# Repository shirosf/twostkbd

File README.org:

* Two-stroke single hand keyboard
** Introduction
This is a following project to [[https://github.com/shirosf/binarykbd][Binary5 keyboard]]
The basic idea of this keyboard is as follows:
+ hit one of 6 keys twice: 36 codes
[[./photos/twostkbd_finger_maps1.png]]
+ 4 modifiers: 'shift','ctrl','alt', and one more 'ext'
[[./photos/twostkbd_finger_maps2.png]]
+ 3 function keys: 'SPACE','BACK SPACE','RETERN'
[[./photos/twostkbd_finger_maps3.png]]
All key maps can be changed by a configuration file

The total uses 13 keys.
26 of the 36 codes are used for alphabet character codes.
The other 10 are used for numerical character codes.
'ext' modifiers support symbol character codes.

** Hardware
KiCAD schematic and PCB data are in 'pcb' directory.
The HW consists of key switches, LEDs and Raspberry Pi Zero.
The circuits are mostly simple connections between GPIOs and switches.
#+ATTR_LATEX: :width 200px
#+ATTR_HTML: :width 200px
#+CAPTION: 14 keys and Raspberry Pi Zero
[[./photos/kbd_photo1.jpg]]

<2024-09-13 Fri>
Supported "Arduino Nano ESP32" to attach on PiZero connector.
#+ATTR_LATEX: :width 200px
#+ATTR_HTML: :width 200px
#+CAPTION: 13 keys and Arduin Nano ESP32
[[./photos/kbd_arduino1.jpg]]
It would be better to have both PiZero connector and Arduino Nano
connector on the PCB.
I would update the PCB design at the time of the next PCB order.
Arduino GBIO connections are defined in "key-gpio table" in "config.org"

** Arduino Software
Arduino project directory is "twskbino".
Go to the directory, then edit "Makefile" there to adjust to your hardware.
My Arduino board was an unofficial "esp32-s3" type board; to find out
"FBQN", I chose a looks-close one.
I believe that as long as it is "esp32-s3" type board "FBQN" should be okay.

To build and install from that Makefile, you need to install "arduino-cli"
and "esp32-s3" library.
Once they are ready, "make install" does all the jobs.

People who use IDE need a different way.

The way of configuration is the same as the PiZero Software.
Everything is defined in "config.org".

Arduino Nano has a RGB-LED on the board.
It starts with non-lighting status(R, G, B are all turned off).
'B' is ON when a key is pressed.
'G' is ON when any modifier key is pressed or locked.

** PiZero Software
*** Installation
Copy following 3 files into some directory of Pi Zero.
+ twostkbd.py, create_device.sh, config.org

Using included Makefile, "make sshcopy" copies the files by 'scp'.
It needs 'pizero' defined in ssh config.

*** Run
You go to the directory of the target Pi Zero where 3 files above are copied
by ssh or a local terminal.

At the first time after booting up, 'create_device.sh' needs to be run.
It creates a USB HID device: '/dev/hidg0'.

Once the USB HID device is created, 'twostkbd.py' can run, and it feeds
keyboard events into the device.

*** systemd service
To make the program start automatically at boot time, install "twostkbd.service"
and enable it as follows:
when you copy "twostkbd.py, create_device.sh, config.org" to the target Pi Zero,
you also copy "Makefile, twostkbd.service". Then go to the directory, and run the
following commands:
$ sudo make install
$ sudo make enable_service

When you changed the program or the config file in the working directory,
$ sudo make install
then restart the service again as next:
$ sudo systemctl restart twostkbd.service

*** Configuration
'twostkbd.py' reads 'config.org' file in the working directory.
'config.org' has the following 4 sections:
+ key-gpio table
  Each row defines,
  "schematic switch symbol","GPIO number","key name in this config file"
  Any key switch position can be changed in this table.
  E.G. swapping 'ctrl' and 'shift' in the table swaps the positions of 'ctrl' key
  and 'shift' key.

+ 6-key table
  Each row defines,
  assigned key: alphabet or number.
  '1st key' and '2nd key' combination by number, which is the number part of 'k*' name.
  modified key by the modifier key.
  The most of 'shift', 'alt', 'ctrl' modifier positions are empty.  In those cases the
  modifiers simply add the named modifier bits on the key events.

+ fkey table
  This table defines the function keys: f0 to f3.

+ multikeys table
  When more than 2 keys are pressed at the same time, it functions as "func" column
  defined function.

** License
Unless otherwise explicitly stated,
all files in this project are released under GNU General Public License Version 2.

** Development history
*** <2024-11-15 Fri>
With a half year practice, I come to around 25-WPM level.
And it seems to be saturated and the progress from this point will be very slow.
For some purposes, this keyboard could be useful.
But for my use, which is mostly writing program codes, it can't replace
regular 2-handed keyboards.

I stop this project at this point.

*** <2024-09-14 Sat>
+ Released the Arduino ESP32-S3 software.
PiZero runs a heavy Linux kernel and takes a long time to boot up.
There must be a room to improve by optimization, but I thought it
wouldn't come to my expected level.
With Arduino HW, connecting a USB cable, it becomes ready to use in a second.
Arduino supports a very convenient USBHIDKeyboard library; thanks to it
developing the software was easy.

+ Created a new board which uses "[[http://www.kailh.com/en/Products/Ks/CS/][Kailh Choc Switch]], Red".
[[./photos/choc_sw_pink_red.jpg]]
I've been using "Pink" with 20g operation force.
It was the lightest operation force in what I could find in the market.
Actuary it is a little too light, and I often hit wrong keys inadvertently.
"Red" with 50g is better for that point.
Pursuing faster typing, however, "Pink" would be better.
I'm still wondering which I should use.

*** <2024-08-03 Sat>
Moved TAB to "multikeys table". "k1,k2,k3" is easier than "shift-f2".
"fkey table" modifier functions are all empty, modifier keys are applied on the all.
Changed MULTIKEY_GAP to 50msec from 30msec.

*** <2024-08-02 Fri>
Changed "multikeys table", "up" and "down" are swapped.

[[./photos/twostkbd_finger_maps4.png]]

[[./photos/twostkbd_finger_maps5.png]]

*** <2024-08-01 Thu>
Refactored the code.
Using "keyqueue", removed multiple timers.
Using "bounce_time" to create Button object, removed the chattering cancellation process.

*** <2024-07-21 Sun>
Tuned "multikeys table" to be convenient for cursor moves.

*** <2024-07-18 Thu>
Removed "fmode table", added "multikeys table" instead.

*** <2024-06-30 Sun>
Published [[https://youtu.be/tp5e6nVgrqI][Youtube Video]].

*** <2024-06-17 Mon>
Modifier keys are difficult to keep holding, especially ALT key.
For a solution, make hitting a modifier key be a locked status for the following
character input.
E.G.
1. hit ALT and release, this locks ALT status
2. input 'x', this becomes ALT-x, and the modifier lock status is released.
When a modifier key is held pressed and a character input happens, the modifier key
is not locked.

*** <2024-06-01 Sat>
Send modifier key events without character key events, so that 'Alt' + 'Mouse click'
type actions can work.

*** <2024-05-25 Sat>
'f0' key is difficult to press. I removed it.
Now, the function keys are 3: 'f1', 'f2' and 'f3'.
'TAB' function is covered by 'shift'+'f2'.

*** <2024-05-14 Tue>
The program basically works okay.
I started practice.

*** <2024-05-10 Fri>
Received PCB

#+OPTIONS: \n:t ^:nil

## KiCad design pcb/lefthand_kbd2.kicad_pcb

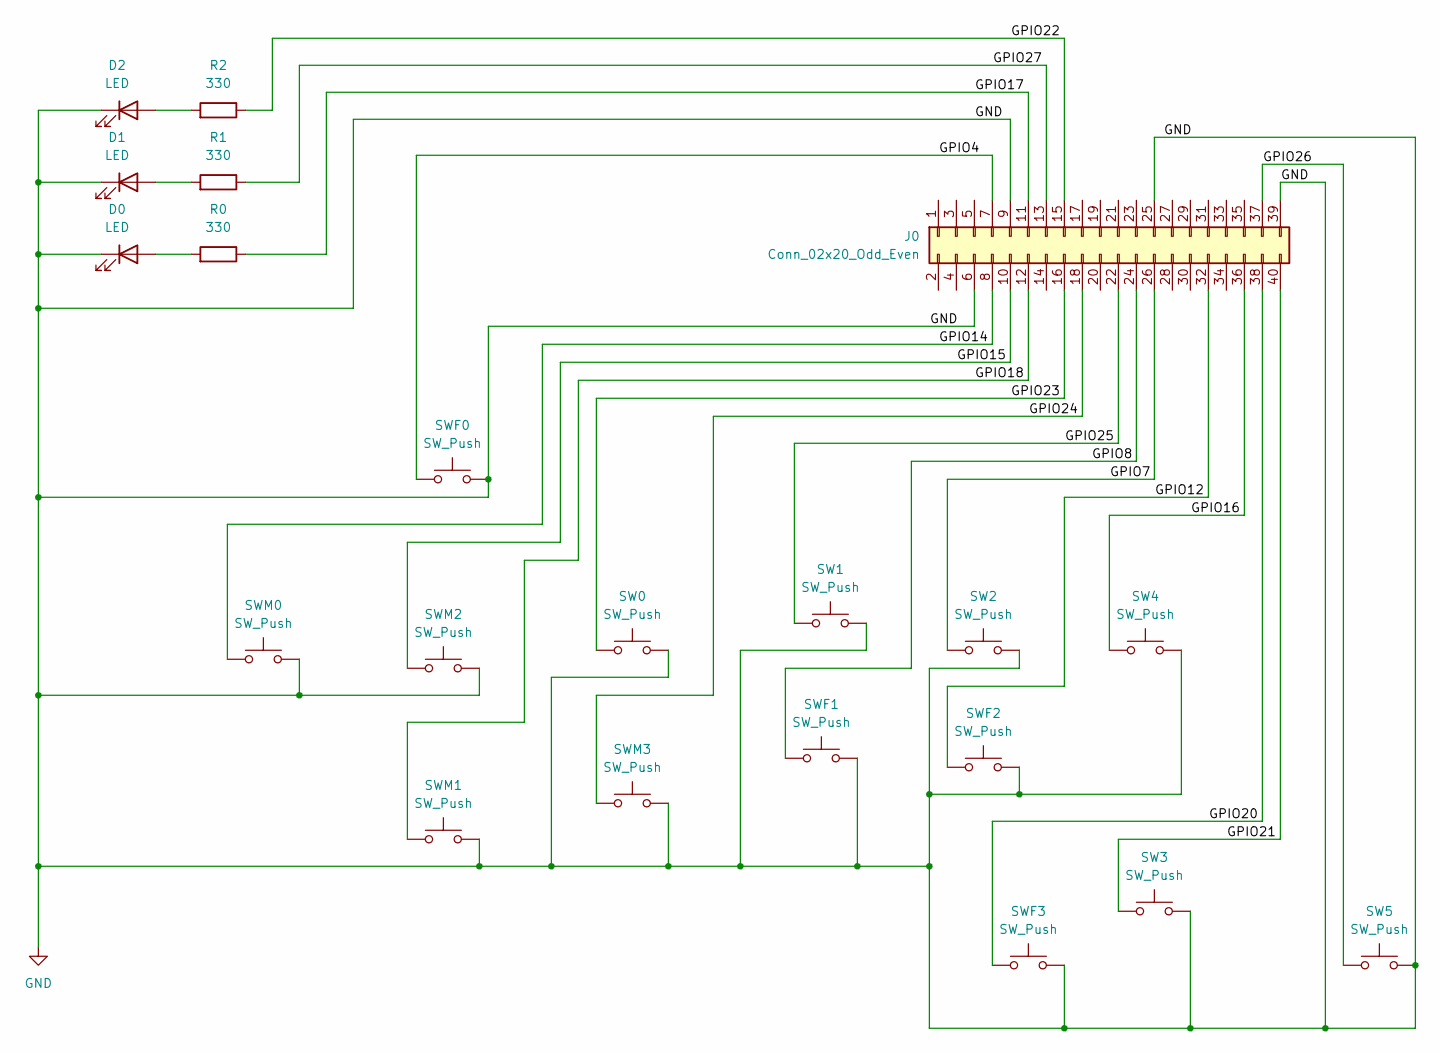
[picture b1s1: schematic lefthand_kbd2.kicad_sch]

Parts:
D0, D1, D2: LED; D_T-1_P2.54mm_Vertical_AnodeUp
J0: Conn_02x20_Odd_Even; Raspberry_Pi_Zero_Socketed_THT_FaceDown_MountingHoles
R0, R1, R2: 330; R_Axial_DIN0204_L3.6mm_D1.6mm_P7.62mm_Horizontal
SW0, SW1, SW2, SW3, SW4, SW5: SW_Push; Kailh_Choc
SWF0, SWF1, SWF2, SWF3: SW_Push; Kailh_Choc
SWM0, SWM1, SWM2, SWM3: SW_Push; Kailh_Choc

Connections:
/GPIO4: J0.7, SWF0.1
/GPIO7: J0.26, SW2.1
/GPIO8: J0.24, SWF1.1
/GPIO12: J0.32, SWF2.1
/GPIO14: J0.8, SWM0.1
/GPIO15: J0.10, SWM2.1
/GPIO16: J0.36, SW4.1
/GPIO17: J0.11, R0.1
/GPIO18: J0.12, SWM1.1
/GPIO20: J0.38, SWF3.1
/GPIO21: J0.40, SW3.1
/GPIO22: J0.15, R2.1
/GPIO23: J0.16, SW0.1
/GPIO24: J0.18, SWM3.1
/GPIO25: J0.22, SW1.1
/GPIO26: J0.37, SW5.1
/GPIO27: J0.13, R1.1
GND: D0.1 (K), D1.1 (K), D2.1 (K), J0.6, J0.9, J0.25, J0.39, SW0.2, SW1.2, SW2.2, SW3.2, SW4.2, SW5.2, SWF0.2, SWF1.2, SWF2.2, SWF3.2, SWM0.2, SWM1.2, SWM2.2, SWM3.2
unnamed: D0.2 (A), R0.2
unnamed: D1.2 (A), R1.2
unnamed: D2.2 (A), R2.2

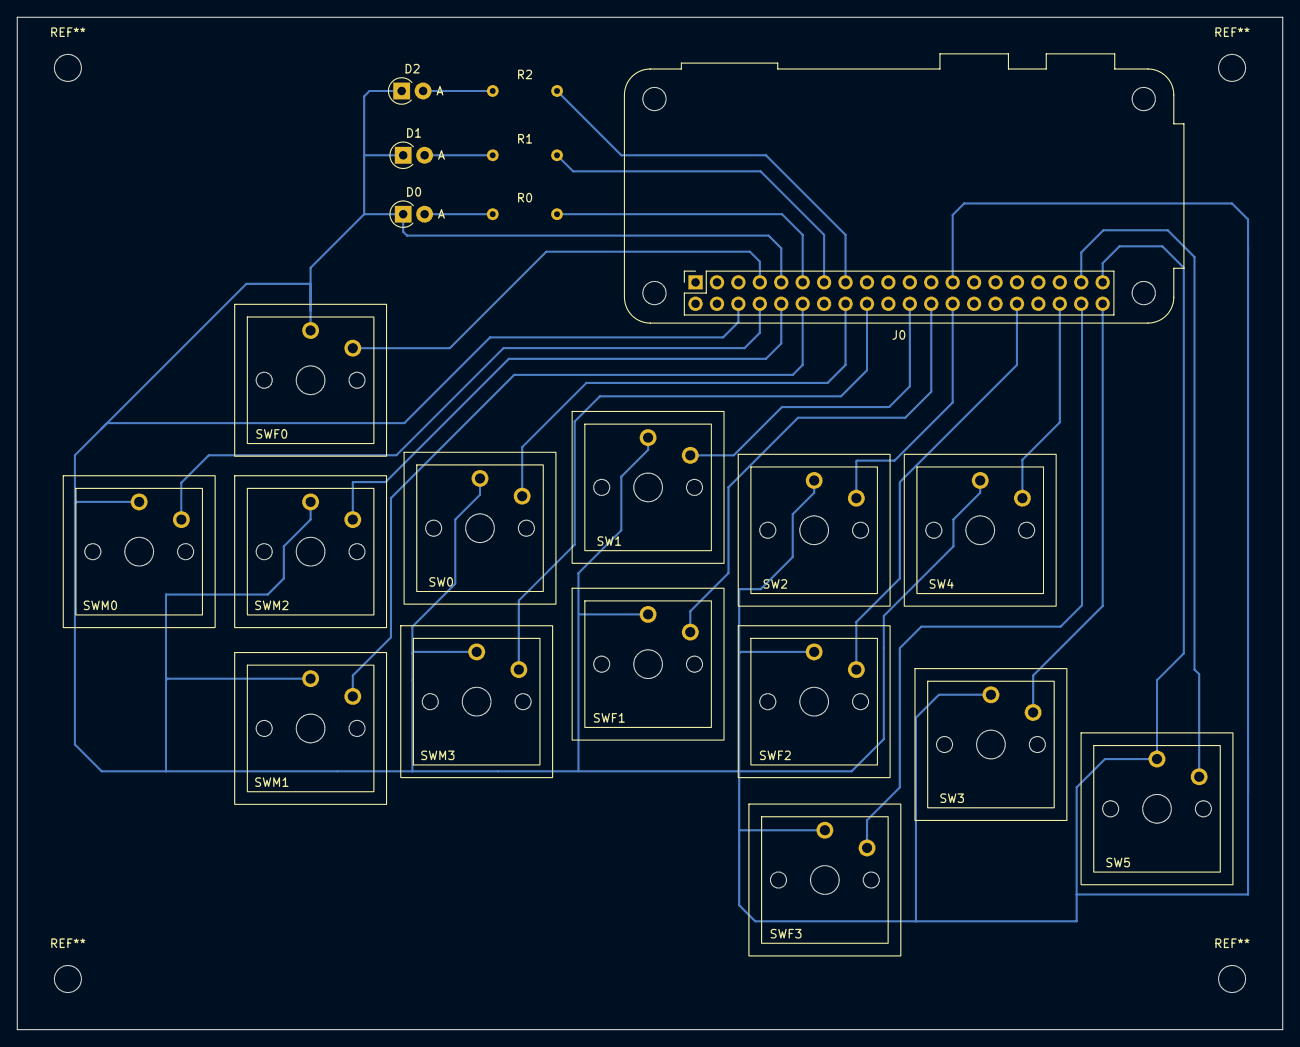
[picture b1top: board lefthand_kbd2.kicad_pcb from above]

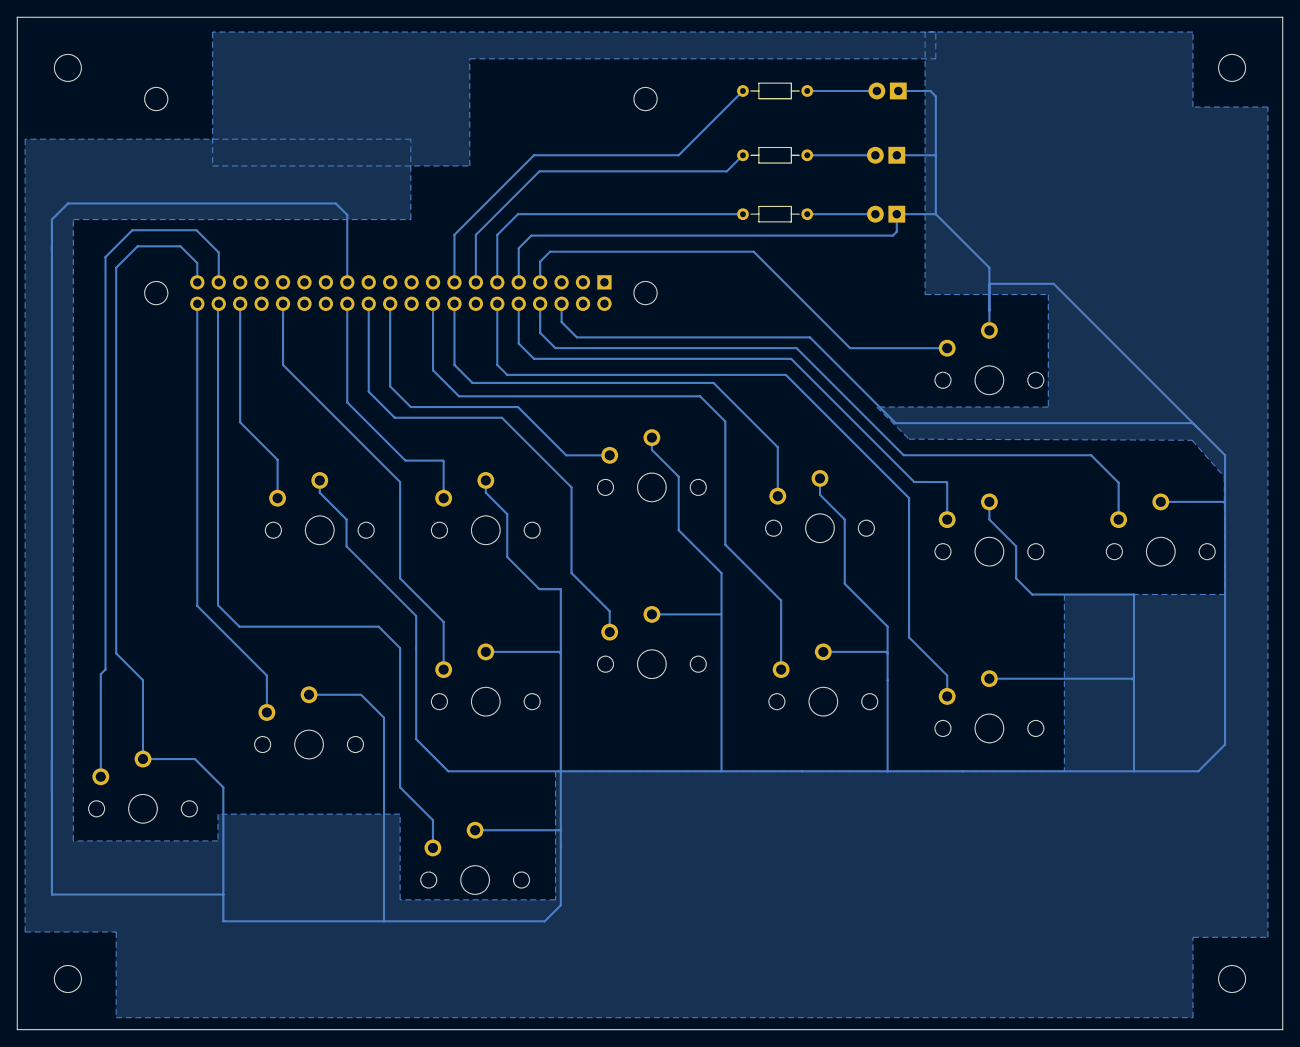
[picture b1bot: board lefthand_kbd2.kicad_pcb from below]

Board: 2 copper layers, 150.0 x 120.0 mm, 21 parts (3 on the bottom side), 21 nets.

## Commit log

2024-05-12 works as a usb keyboard
2024-05-13 new config
2024-05-13 add .gitignore
2024-05-14 add kicad files
2024-05-15 print key table
2024-05-16 all keys are defined in the table
2024-05-16 add check_fmode_switch
2024-05-18 debugging check_fmode_switch
2024-05-18 support fmode
2024-05-19 use threading wait for infinite loop
2024-05-19 add README.org
2024-05-21 detect a rising edge only after the guard time
2024-05-22 config instruction in REARME
2024-05-25 add tskpractice.py
2024-06-01 support modifier key only events
2024-06-22 mod key lock for the following action
2024-06-30 update REDEME
2024-07-20 multiple keys functions, another method
2024-07-20 fix a problem after multi keys
2024-07-21 add new photos
2024-07-23 use CHATTERING_GUARD_REL_NS
2024-08-01 refactored by using "keyqueue"
2024-08-01 clear multi keys when no matched combinations
2024-08-03 fix missing relese events
2024-08-03 move TAB to mulitkeys table
2024-08-03 keep modkeys bits at the release time
2024-08-18 use LED1 and LED2
2024-08-18 use twostkbd.py to gnerate C header
2024-08-18 start testing with Arduino esp32-s3
2024-08-21 add fifo_queue
2024-08-23 print key index
2024-08-25 refacter to be general c++ codes
2024-08-25 check_possible_multikeys skips the first key with the gap
2024-08-25 test run on a pc
2024-08-31 change fifo data to a link list
2024-09-01 adding key events functions
2024-09-01 pc build in a different directory
2024-09-03 reg. keys work
2024-09-11 arduino version covers all the functions
2024-09-13 use pressRaw for modifier keys
2024-09-14 updated README.org
2024-09-14 fix a multiple modifier keys issue
2024-09-14 fix release of sequence keys
2024-09-16 fixed the modkeys sequence
2024-09-17 fix cases when release events come with press events
2024-10-14 change the configuration, add Ctl-w,Ctl-y
